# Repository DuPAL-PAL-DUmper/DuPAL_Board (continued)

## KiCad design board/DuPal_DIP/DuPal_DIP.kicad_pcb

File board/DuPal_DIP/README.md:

# DuPAL board

## DISCLAIMER

Any use of this project is **under your own responsibility**.
You will be responsible of checking the correct construction and functionality of your board and the compatiblity of the chips You will insert into it.
By using this project You will agree that I cannot be held responsible if it will destroy any of your devices, damage your computer, burn down your house or whatever.

**Do NOT come to me for hand-holding** using this. It is NOT a plug-and-play tool, and it is something I created **for my own use** and I released in case someone might have an use for it.

## Introduction

The DuPAL board is a simple circuit that mounts an AVR MCU (A classic ATmega328P of Arduino fame), three 74HC595 SIPO registers, one 74HCT166 PISO register, a MAX232 to adapt the serial port to RS232, a linear voltage regulator and a bunch of other passive components.

This board was designed and built to help myself bruteforce PAL devices. It has the hardware facilities necessary to scan all the inputs of the PAL, to check whether an output is high, low or hi-z and to report back the status to the host.

Details on how the features are implemented can be found on the Firmware's repository.

## Software

### Bootloader

This board uses the [Optiboot Bootloader](https://github.com/Optiboot/optiboot), currently at version 8.0, built for an **ATMega328** running at 20Mhz, and with a baudrate of 57600bps.

The command line to build the bootloader is

```shell
make atmega328 AVR_FREQ=20000000L LED_START_FLASHES=8 BAUD_RATE=57600
```

See [Compiling Optiboot](https://github.com/Optiboot/optiboot/wiki/CompilingOptiboot) for details.

The resulting bootloader can then be loaded via the ISP header. For example, by using `avrdude` and an **AVR Dragon** programmer:

```shell
avrdude  -c dragon_isp -P usb \
  -p atmega328p -e -u -U efuse:w:0xFD:m -U hfuse:w:0xDE:m \
  -U lfuse:w:0xFF:m -U flash:w:optiboot_atmega328.hex
```

### Firmware

Details on the firmware can be found on the **DuPAL_Firmware** repository.

## Hardware

The board was designed with [KiCad](https://kicad.org/) EDA.

In its current form, the board is a pretty simple build, using exclusively through-hole components.

### Powering the board

The board can be powered with a DC supply voltage between 7.5V and 9V, 12V is possible but the regulator starts to get hot.

The power connector has a positive tip, and is protected against reverse voltage by a 1N4001 diode.

### Bill of Materials

- **SW2** - Sliding SPST switch, pin spacing is 2mm, the outer 2 pins are just for mechanical stability
- **J1** - 3x2 pins 2.54mm pcb male header
- **C4, C5, C6 & C7** - 4x 1uF / 35v min electrolytic capacitors
- **C15** - 1x 0.22uF / 35v min electrolytic capacitor
- **C3, C8, C9, C10, C11, C12, C13, C14, C16, C17** - 10x 100nF ceramic bypass capacitors
- **C1 & C2** - 2x 22pF NP0 ceramic capacitors
- **R18** - 1x 1Mohm 1/4W resistor
- **R17** - 1x 1.2k 1/4W resistor
- **R16, R19 & R20** - 3x 680ohm 1/4W resistor
- **R1, R2, R3, R4, R5, R6, R7, R8 & R15**, 9x 10Kohm 1/4W resistors
- **D1, D2, D4 & D5** - 4x 3mm LED (recommended red for power, green for activity)
- **J3** - Power supply female barrel connector
- **J2** - DB9 female angled connector
- **SW1** - 4 pin push button
- **D3** - 1N4001 diode
- **U2, U3 & U9** - 3x 74HC595
- **U8** - 1x 74HCT166
- **U6** - MAX232
- **U7** - 7805 TO220 regulator
- **U1** - ATMega328p
- **Y1** - 20Mhz HC49 crystal
- **U5** - 20pin slim ZIF socket
- **U10** - 24pin slim ZIF socket
- *Heat sink for the power regulator (optional, but recommended)*
- *5x 16pin socket (optional)*
- *1x 28pin slim socket (optional)*

Thanks @Porchy for the updated BOM.

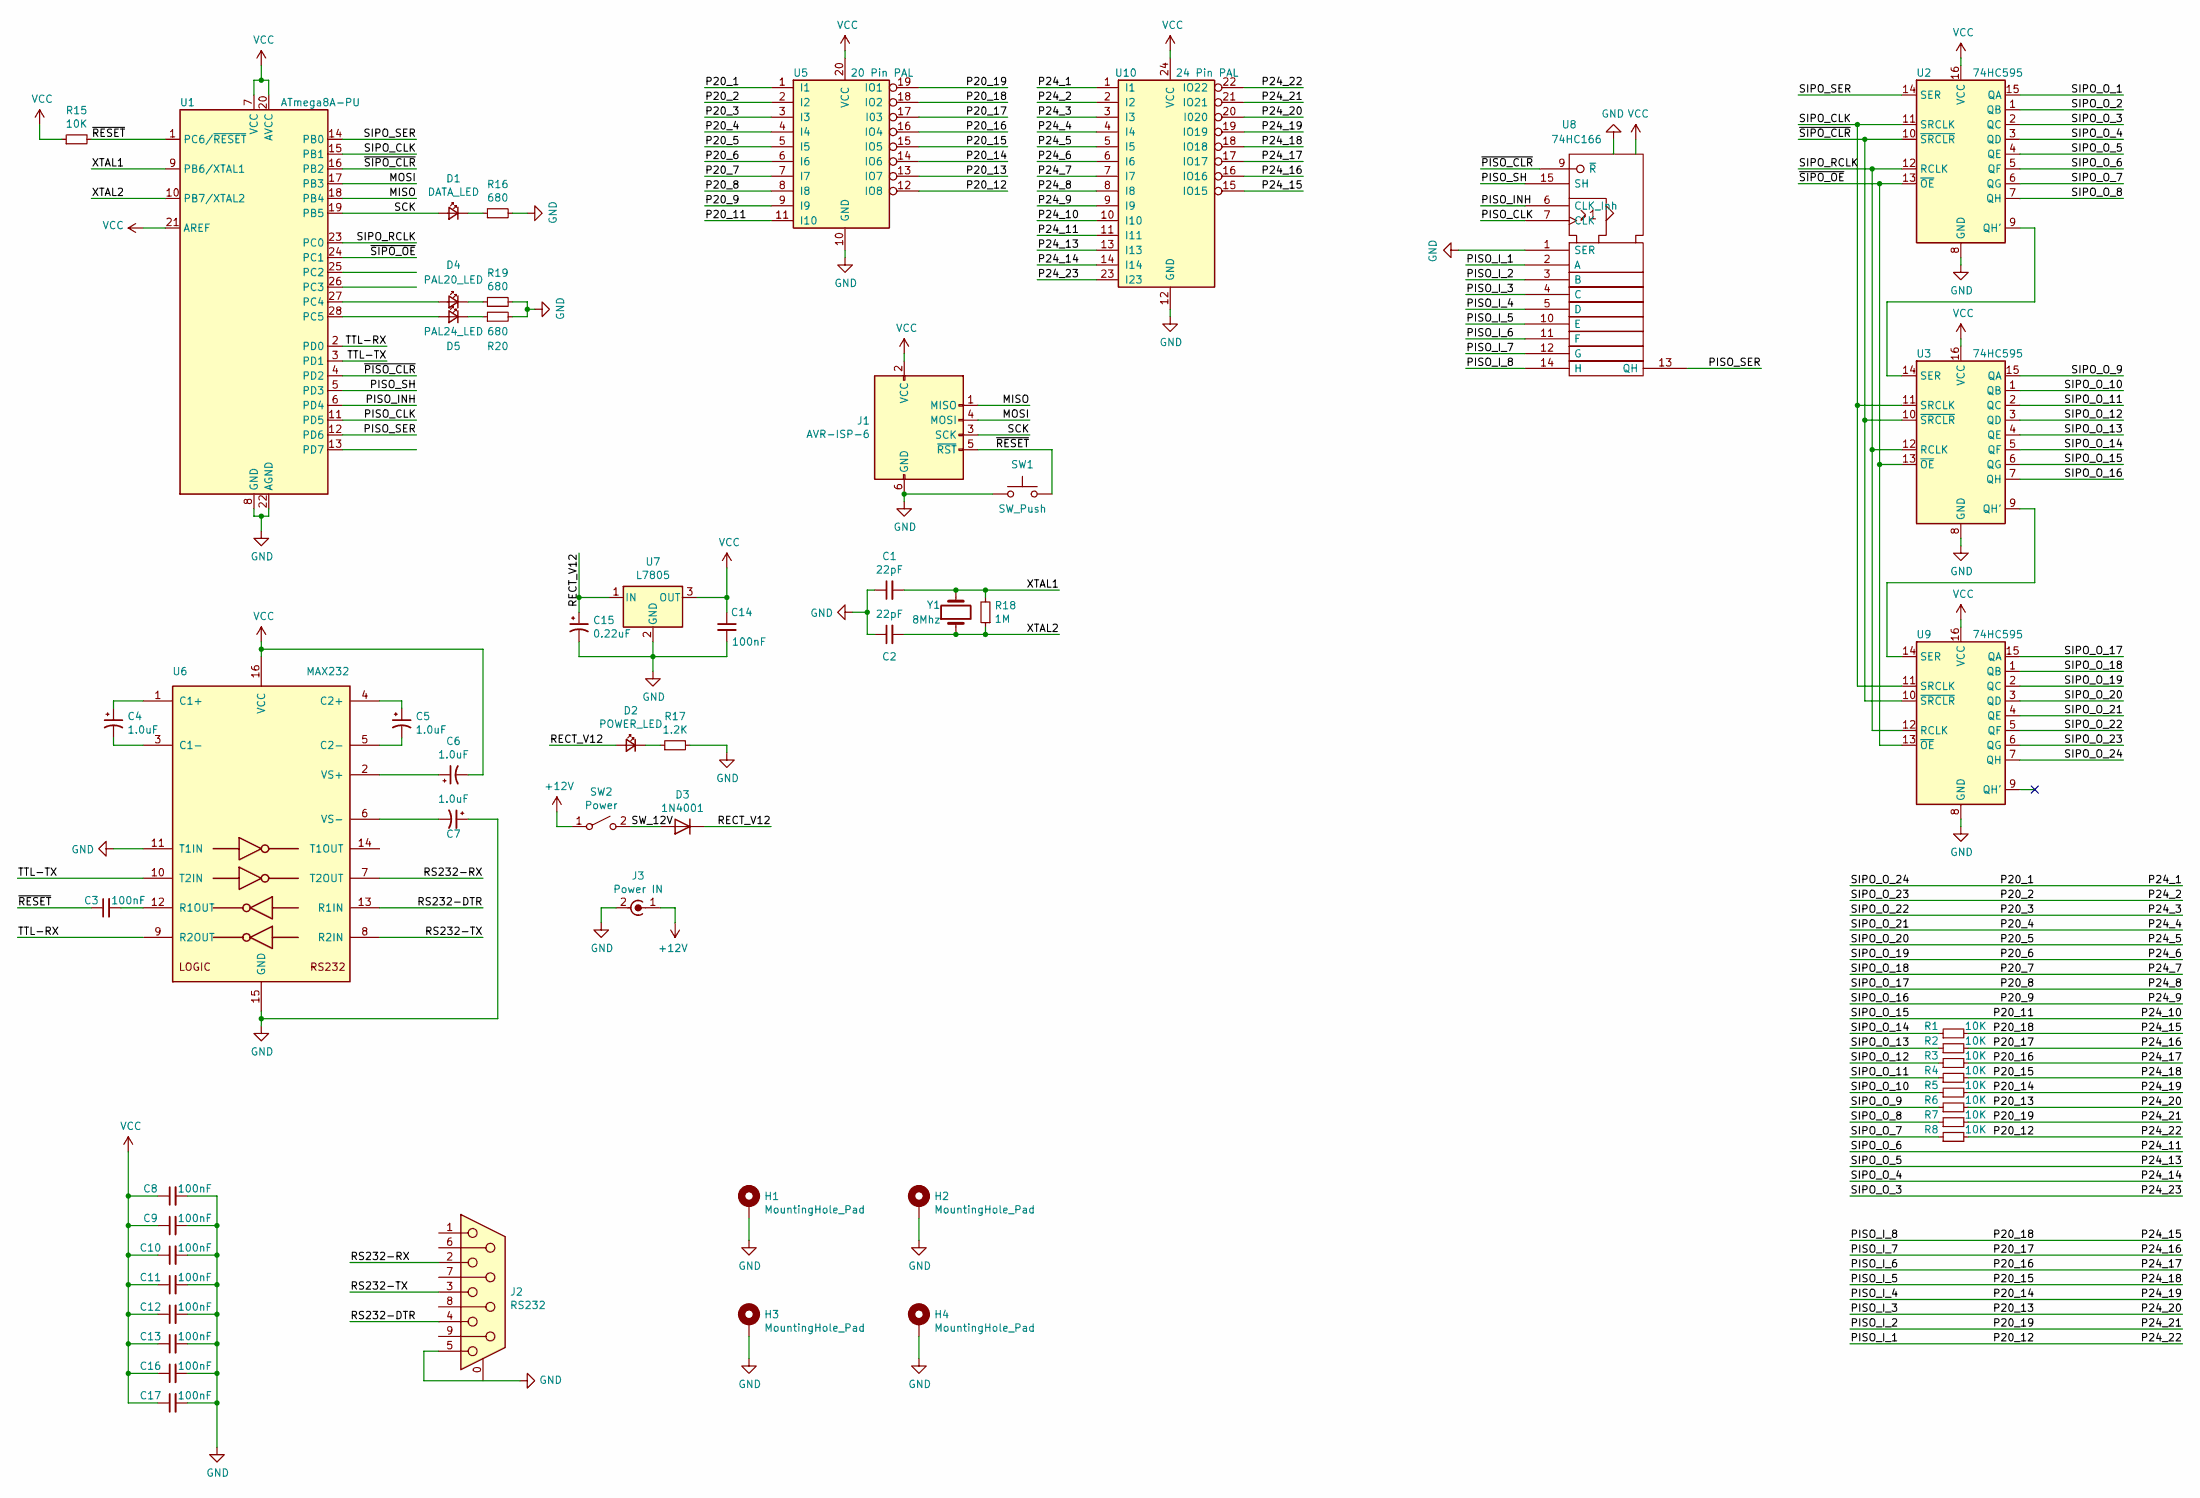
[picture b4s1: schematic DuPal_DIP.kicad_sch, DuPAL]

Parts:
C1, C2: 22pF; C_Disc_D3.0mm_W2.0mm_P2.50mm
C3, C8, C9, C10, C11, C12, C13, C14, C16, C17: 100nF; C_Disc_D3.4mm_W2.1mm_P2.50mm
C4, C5, C6, C7: 1.0uF; CP_Radial_D5.0mm_P2.50mm
C15: 0.22uF; CP_Radial_D5.0mm_P2.50mm
D1: DATA_LED; LED_D2.0mm_W4.8mm_H2.5mm_FlatTop
D2: POWER_LED; LED_D2.0mm_W4.8mm_H2.5mm_FlatTop
D3: 1N4001; D_DO-41_SOD81_P10.16mm_Horizontal
D4: PAL20_LED; LED_D2.0mm_W4.8mm_H2.5mm_FlatTop
D5: PAL24_LED; LED_D2.0mm_W4.8mm_H2.5mm_FlatTop
H1, H2, H3, H4: MountingHole_Pad; MountingHole_2.7mm_M2.5_ISO7380_Pad
J1: AVR-ISP-6; IDC-Header_2x03_P2.54mm_Vertical
J2: RS232; DSUB-9_Female_Horizontal_P2.77x2.84mm_EdgePinOffset4.94mm_H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
J3: Power IN; BarrelJack_Horizontal
R1, R2, R3, R4, R5, R6, R7, R8, R15: 10K; R_Axial_DIN0204_L3.6mm_D1.6mm_P7.62mm_Horizontal
R16, R19, R20: 680; R_Axial_DIN0204_L3.6mm_D1.6mm_P7.62mm_Horizontal
R17: 1.2K; R_Axial_DIN0204_L3.6mm_D1.6mm_P7.62mm_Horizontal
R18: 1M; R_Axial_DIN0204_L3.6mm_D1.6mm_P7.62mm_Horizontal
SW1: SW_Push; SW_PUSH_6mm
SW2: Power; SW_Slide_1P2T_CK_OS102011MS2Q
U1: ATmega8A-PU; DIP-28_W7.62mm
U2, U3, U9: 74HC595; DIP-16_W7.62mm
U5: 20 Pin PAL; DIP_Socket-20_W4.3_W5.08_W7.62_W10.16_W10.9_3M_220-3342-00-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
U6: MAX232; DIP-16_W7.62mm
U7: L7805; TO-220-3_Horizontal_TabDown
U8: 74HC166; DIP-16_W7.62mm
U10: 24 Pin PAL; DIP_Socket-24_W4.3_W5.08_W7.62_W10.16_W10.9_3M_224-5248-00-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
Y1: 8Mhz; Crystal_HC49-U_Vertical

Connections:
+12V: J3.1 (In), SW2.1 (A)
/MISO: J1.1 (MISO), U1.18 (PB4)
/MOSI: J1.4 (MOSI), U1.17 (PB3)
/P20_1: U5.1 (I1), U9.7 (QH), U10.1 (I1)
/P20_2: U5.2 (I2), U9.6 (QG), U10.2 (I2)
/P20_3: U5.3 (I3), U9.5 (QF), U10.3 (I3)
/P20_4: U5.4 (I4), U9.4 (QE), U10.4 (I4)
/P20_5: U5.5 (I5), U9.3 (QD), U10.5 (I5)
/P20_6: U5.6 (I6), U9.2 (QC), U10.6 (I6)
/P20_7: U5.7 (I7), U9.1 (QB), U10.7 (I7)
/P20_8: U5.8 (I8), U9.15 (QA), U10.8 (I8)
/P20_9: U3.7 (QH), U5.9 (I9), U10.9 (I9)
/P20_11: U3.6 (QG), U5.11 (I10), U10.10 (I10)
/P20_12: R8.2, U5.12 (IO8), U8.2 (A), U10.22 (IO22)
/P20_13: R6.2, U5.13 (IO7), U8.4 (C), U10.20 (I020)
/P20_14: R5.2, U5.14 (IO6), U8.5 (D), U10.19 (IO19)
/P20_15: R4.2, U5.15 (IO5), U8.10 (E), U10.18 (IO18)
/P20_16: R3.2, U5.16 (IO4), U8.11 (F), U10.17 (IO17)
/P20_17: R2.2, U5.17 (I03), U8.12 (G), U10.16 (IO16)
/P20_18: R1.2, U5.18 (IO2), U8.14 (H), U10.15 (IO15)
/P20_19: R7.2, U5.19 (IO1), U8.3 (B), U10.21 (IO21)
/P24_11: U2.5 (QF), U10.11 (I11)
/P24_13: U2.4 (QE), U10.13 (I13)
/P24_14: U2.3 (QD), U10.14 (I14)
/P24_23: U2.2 (QC), U10.23 (I23)
/PISO_CLK: U1.11 (PD5), U8.7 (CLK)
/PISO_INH: U1.6 (PD4), U8.6 (CLK_Inh)
/PISO_SER: U1.12 (PD6), U8.13 (QH)
/PISO_SH: U1.5 (PD3), U8.15 (SH)
/RECT_V12: C15.1, D2.2 (A), D3.1 (K), U7.1 (IN)
/RS232-DTR: J2.4, U6.13 (R1IN)
/RS232-RX: J2.2, U6.7 (T2OUT)
/RS232-TX: J2.3, U6.8 (R2IN)
/SCK: D1.2 (A), J1.3 (SCK), U1.19 (PB5)
/SIPO_CLK: U1.15 (PB1), U2.11 (SRCLK), U3.11 (SRCLK), U9.11 (SRCLK)
/SIPO_O_1: U2.15 (QA)
/SIPO_O_2: U2.1 (QB)
/SIPO_O_7: R8.1, U2.6 (QG)
/SIPO_O_8: R7.1, U2.7 (QH)
/SIPO_O_9: R6.1, U3.15 (QA)
/SIPO_O_10: R5.1, U3.1 (QB)
/SIPO_O_11: R4.1, U3.2 (QC)
/SIPO_O_12: R3.1, U3.3 (QD)
/SIPO_O_13: R2.1, U3.4 (QE)
/SIPO_O_14: R1.1, U3.5 (QF)
/SIPO_RCLK: U1.23 (PC0), U2.12 (RCLK), U3.12 (RCLK), U9.12 (RCLK)
/SIPO_SER: U1.14 (PB0), U2.14 (SER)
/SW_12V: D3.2 (A), SW2.2 (B)
/TTL-RX: U1.2 (PD0), U6.9 (R2OUT)
/TTL-TX: U1.3 (PD1), U6.10 (T2IN)
/XTAL1: C1.2, R18.2, U1.9 (PB6/XTAL1), Y1.2
/XTAL2: C2.2, R18.1, U1.10 (PB7/XTAL2), Y1.1
/~PISO_CLR: U1.4 (PD2), U8.9 (~R)
/~RESET: C3.1, J1.5 (~RST), R15.2, SW1.2, U1.1 (PC6/~RESET)
/~SIPO_CLR: U1.16 (PB2), U2.10 (~SRCLR), U3.10 (~SRCLR), U9.10 (~SRCLR)
/~SIPO_OE: U1.24 (PC1), U2.13 (~OE), U3.13 (~OE), U9.13 (~OE)
GND: C1.1, C2.1, C7.1, C8.2, C9.2, C10.2, C11.2, C12.2, C13.2, C14.2, C15.2, C16.2, C17.2, H1.1, H2.1, H3.1, H4.1, J1.6 (GND), J2.0 (PAD), J2.5, J3.2 (Ext), R16.2, R17.2, R19.2, R20.2, SW1.1, U1.8 (GND), U1.22 (AGND), U2.8 (GND), U3.8 (GND), U5.10 (GND), U6.11 (T1IN), U6.15 (GND), U7.2 (GND), U8.1 (SER), U8.8 (GND), U9.8 (GND), U10.12 (GND)
unnamed: C3.2, U6.12 (R1OUT)
unnamed: C4.1, U6.1 (C1+)
unnamed: C4.2, U6.3 (C1-)
unnamed: C5.1, U6.4 (C2+)
unnamed: C5.2, U6.5 (C2-)
unnamed: C6.1, U6.2 (VS+)
unnamed: C7.2, U6.6 (VS-)
unnamed: D1.1 (K), R16.1
unnamed: D2.1 (K), R17.1
unnamed: D4.1 (K), R19.1
unnamed: D4.2 (A), U1.27 (PC4)
unnamed: D5.1 (K), R20.1
unnamed: D5.2 (A), U1.28 (PC5)
unnamed: U2.9 (QH'), U3.14 (SER)
unnamed: U3.9 (QH'), U9.14 (SER)
VCC: C6.2, C8.1, C9.1, C10.1, C11.1, C12.1, C13.1, C14.1, C16.1, C17.1, J1.2 (VCC), R15.1, U1.7 (VCC), U1.20 (AVCC), U1.21 (AREF), U2.16 (VCC), U3.16 (VCC), U5.20 (VCC), U6.16 (VCC), U7.3 (OUT), U8.16 (VCC), U9.16 (VCC), U10.24 (VCC)

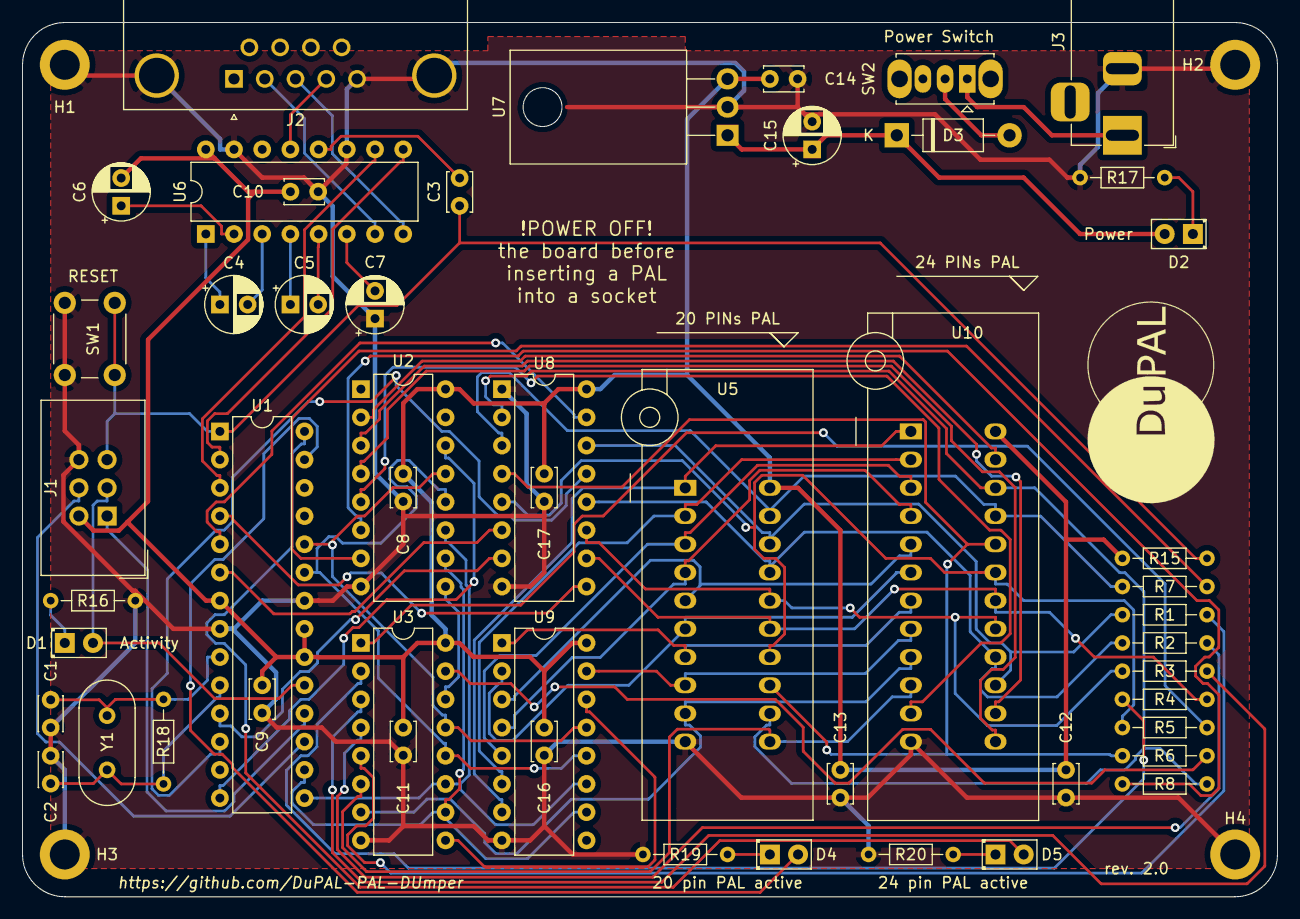
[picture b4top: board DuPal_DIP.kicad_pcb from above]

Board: 2 copper layers, 113.0 x 78.7 mm, 55 parts (0 on the bottom side), 71 nets.

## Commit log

2020-02-25 Begin schematic
2020-02-25 Add DuPal schematics changes
2020-02-25 Add oscillator
2020-02-25 More schematis changes
2020-02-25 Complete schematic of PAL dumper
2020-02-26 Change wiring
2020-02-26 Assigned footprints
2020-02-26 Add correct footprints
2020-02-26 Organized board
2020-02-26 DuPAL project
2020-02-26 Add logo
2020-02-26 Add front silk text
2020-02-26 Add gerbers
2020-02-27 Distance some ICs
2020-08-11 Start writing the readme for the PCB board
2020-08-11 Update BOM
2020-08-11 Fill in the README
2020-08-13 Add LICENSE.txt
2020-08-14 Add changelog and updated readme
2020-08-15 Added PCB pics, added a TODO
2020-08-15 Add rev1.1 board
2020-08-15 Typo in changelog
2020-08-16 Begin adding new shift and parallel registers
2020-08-16 Begin remapping the connections
2020-08-16 Slight cleanup
2020-08-16 Begin connecting the new ICs in the circuit
2020-08-16 Add 24 pin slot
2020-08-16 Connected both PAL outputs
2020-08-16 Reworked the outputs and added the inputs to the new PAL
2020-08-16 Cleanup schematics, removed unused IC
2020-08-16 Assign more footprints and names
2020-08-16 Begin reworking the PCB
2020-08-16 First PCB model for Rev.2
2020-08-16 Add some silkscreen changes
2020-08-16 More silkscreen changes
2020-08-16 Add kicad files and pcb pic
2020-08-16 Add rev.2 pic
2020-08-16 Updated silkscreen
2020-09-28 Revert "Update README"
    This reverts commit 14c9aec4713ba785e934c3e93f074ddb65a57178.
2020-11-01 Updated the BOM
2021-04-11 Add Disclaimer
2021-04-11 Additional README
2021-06-07 Added TODO in readme
2021-06-07 Fixed TODO
2021-11-02 Fix BOM list, missing C5
2021-11-08 Update README.md
    https://forum.kicad.info/t/warning-avoid-all-links-to-kicad-pcb-org-use-kicad-org/31521
2021-11-09 Update KiCad URL
2024-01-02 Add cache file
2024-01-02 Add cache
2024-01-02 Update project, add schematics
2024-06-16 Begin drawing V3 board
2024-06-16 Change resistor value
2024-06-16 Add connections to pico
2024-06-16 Add pulldown resistors for socket
2024-06-16 Change pulldown res on switched VCC value
2024-06-16 Added mounting holes
2024-06-16 Cleanup
2024-06-16 Begin organizing the footprint
2024-06-17 Some more placing on the PCB
2024-06-17 More board placing
2024-06-17 More placing
2024-06-18 Update board
2024-06-18 More placements
2024-06-21 Initial placement on board
2024-06-21 First automatic routing of the board
2024-06-22 Update silkscreen
2024-06-26 Update silkscreen on the board
2024-06-27 Gerbers for rev0
2024-07-08 Add external pullup on /RELAY_ENABLE pin to avoid triggering at powerup
2024-07-09 Fix missing connection on a shifter
2024-07-13 Add pinheaders in schematic
2024-07-16 Add pinheaders to rev. 1 V3 board
2024-07-16 Move some silkscreen around
2024-07-16 Allow usage of a 48pin zif dip
2024-07-16 Add silkscreen indication on where you should install a 42pin zif
2024-07-22 Add gerbers for rev1 of dupal v3
2024-07-22 Begin drawing a pod to read 1702/2708 eproms
2024-07-22 First sketch of the boarx
2024-07-22 Add automatic routing for pod
2024-07-23 Add pod for PAL devices
2024-07-26 Add rev.1 for the pal pod
2024-07-26 Moved some of the readmes
2024-07-26 Change relative links
2024-07-26 Ok, stop using relative paths
2024-07-26 Fix dupal v3 picture
2024-07-26 Add schematics pdf for dupico, add pcbway sponsorship
2024-07-26 Move sponsorship to main README
2024-07-26 Remove TODO
2024-07-26 Renamed 1702A pod with correct name
2024-07-29 Begin cleaning up some egregious clearance rule violations
2024-07-29 Avoid clearance violations, create rev.2 board for dupico
2024-07-30 Update BOM for dupico
2024-07-30 Fix one entry in dupico BOM
2024-08-01 Update dupico readme
2024-08-01 Fix BOM for dupico
2024-08-01 Add readme for the pal pod
2024-08-01 fix typos
2024-08-01 Update headers of the READMEs for dupico and pod pal
2024-08-11 Remove useless image
2024-08-12 Update pal pod for dupico
2024-08-12 Update README of the PAL pod for dupico
2024-08-12 Fix typo
2024-08-12 Fix rotated transistor in dupico pal pod
2024-08-12 Add a note to the README
2024-08-13 Add PCBWay project link
2024-08-13 Update the README for the PAL POD linking PCBway shared project
2024-08-15 Fixed typos in BOM
    Changed R42, R46 - R85 resistor values to 470k as stated in schematics from the 10k that's listed.
    Changed SB74LV1T125DBV to SN74LV1T125DBV as found on Mouser
2024-08-17 Add a warning on the README for the dupico
2024-08-18 Add eprom_01 board
2024-08-18 Shift the ZIF32 socket on the eprom_01 pod
2024-09-03 Add schematics and gerbers
2024-09-03 Update EPROM_01 POD readme and pic
2024-09-03 Remove old errata from EPROM_01
2024-09-03 Add PCBWay reference
2024-09-12 Fix EPROM pod power selection table
2025-02-17 Updated BOM for DuPAL V3 to include D1
2026-03-03 Fix a typo in BOM
